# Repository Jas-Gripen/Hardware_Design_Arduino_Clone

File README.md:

# Hardware_Design_Arduino_Clone
I made schematics for an Arduino Clone in KiCad.
There is a description of why I chosed to design the board like I did in the PCB_Report.pdf file.

The original schematic (only Eeschema type) are avalible here: https://www.arduino.cc/en/uploads/Main/arduino_NG_schematic.png
The placement of the components as well as the version of them are of my own choosing. The same goas for the PCB-traces and vias.

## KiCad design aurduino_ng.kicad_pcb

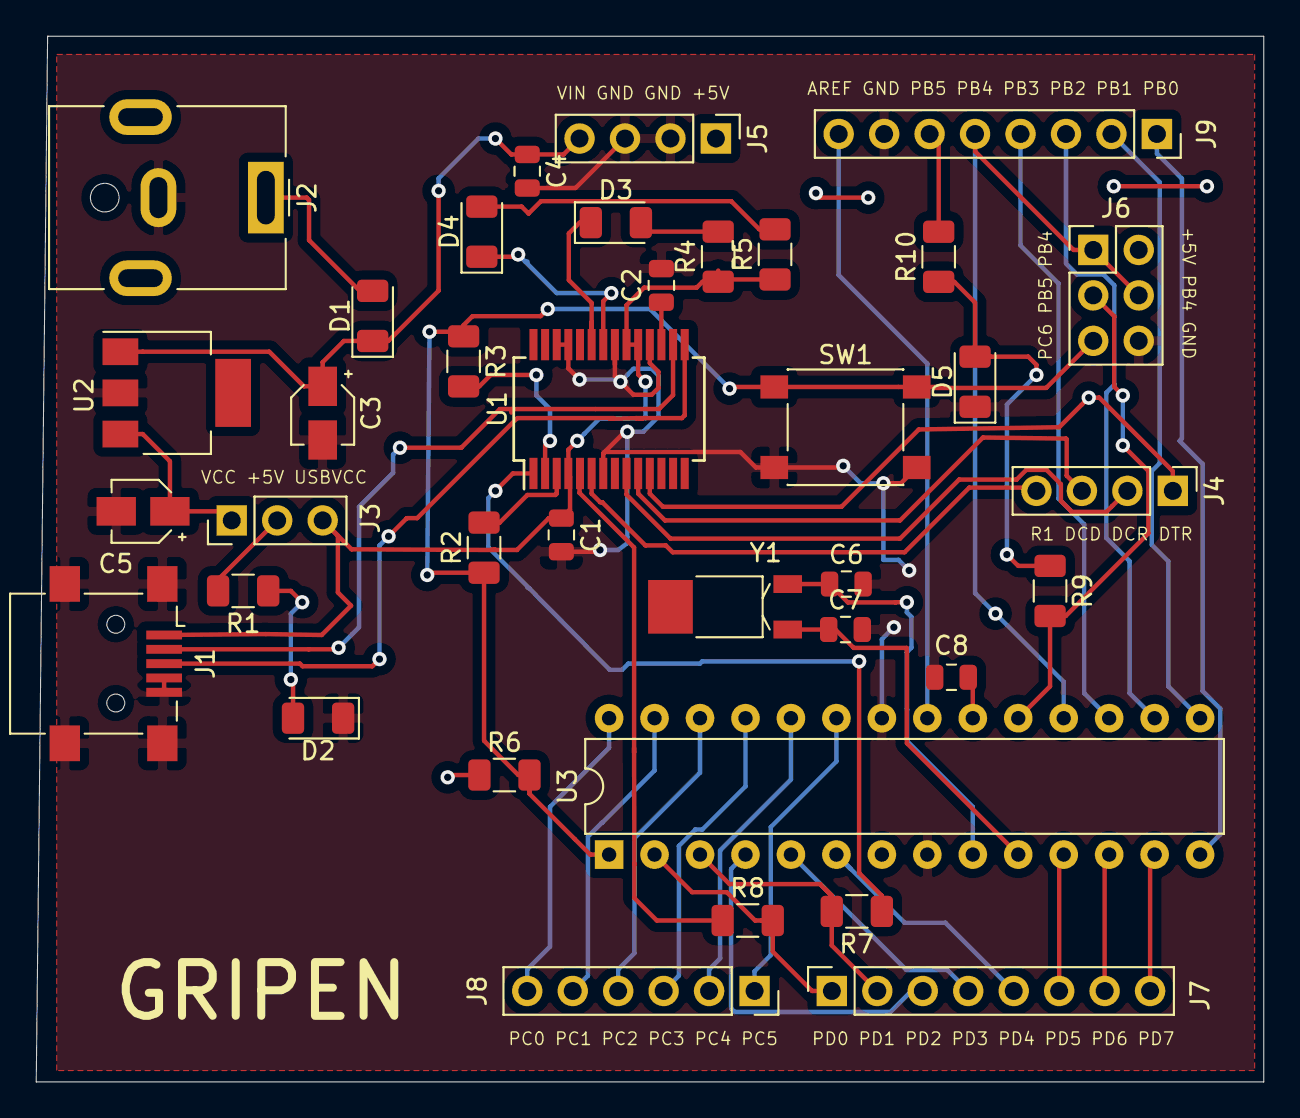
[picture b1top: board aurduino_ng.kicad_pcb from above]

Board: 2 copper layers, 68.6 x 58.4 mm, 37 parts (0 on the bottom side), 48 nets.

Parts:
C1, C2, C4, C8: 100n; C_0805_2012Metric
C3, C5: 100u; CP_Elec_3x5.3
C6, C7: 22p; C_0805_2012Metric
D1, D2, D3, D4, D5: LED; LED_1206_3216Metric
J1: USB_B_Mini; USB_Mini-B_Lumberg_2486_01_Horizontal
J2: Barrel_Jack_Switch; BarrelJack_CUI_PJ-063AH_Horizontal
J3: Conn_01x03; PinHeader_1x03_P2.54mm_Vertical
J4, J5: Conn_01x04; PinHeader_1x04_P2.54mm_Vertical
J6: Conn_02x03_Odd_Even; PinHeader_2x03_P2.54mm_Vertical
J7: Conn_01x06_Female; PinSocket_1x06_P2.54mm_Vertical
J8, J9: Conn_01x08_Female; PinSocket_1x08_P2.54mm_Vertical
R1, R9, R10: 470; R_1206_3216Metric
R2, R3: 100; R_1206_3216Metric
R4, R5: 220; R_1206_3216Metric
R6: 10k; R_1206_3216Metric
R7, R8: 1k; R_1206_3216Metric
SW1: SW_DIP_x01; SW_SPST_PTS645
U1: FT232RL_my; SSOP-28_5.3x10.2mm_P0.65mm
U2: L7805; SOT-223
U3: ATmega8-16PU; DIP-28_W7.62mm
Y1: 16MHz; Crystal_SMD_MicroCrystal_MS1V-T1K

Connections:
+5V: C8.1, J3.2, J5.1, J6.2, R1.2, R6.1, U3.7, U3.20
/AREF: J9.8, U3.21
/M8RXD: R8.1, U1.5
/M8TXD: R7.1, U1.1
/PB4: J6.1, J6.4, J9.5, U3.18
/PB5: J6.3, R9.2, U3.19
/PD0: J8.1, R8.2, U3.2
/PD1: J8.2, R7.2, U3.3
/USBVCC: C1.1, J1.1, J3.3, R4.1, R5.1, U1.4, U1.19, U1.20
/VCC: C5.1, J3.1, U2.3
/VIN: C3.1, C4.1, D1.1, J5.4, U2.1
GND: C1.2, C2.2, C3.2, C4.2, C5.2, C6.2, C7.2, C8.2, D2.1, D5.1, J1.4, J1.5, J1.6, J2.2, J5.2, J5.3, J6.6, J9.7, SW1.2, U1.7, U1.18, U1.21, U1.25, U1.26, U2.2, U3.8, U3.22
unnamed: C2.1, U1.17
unnamed: C6.1, U3.9, Y1.1
unnamed: C7.1, U3.10, Y1.2
unnamed: D1.2, J2.1
unnamed: D2.2, R1.1
unnamed: D3.1, U1.23
unnamed: D3.2, R4.2
unnamed: D4.1, U1.22
unnamed: D4.2, R5.2
unnamed: D5.2, R9.1, R10.1
unnamed: J1.2, U1.16
unnamed: J1.3, U1.15
unnamed: J4.1, U1.11
unnamed: J4.2, U1.9
unnamed: J4.3, U1.10
unnamed: J4.4, U1.6
unnamed: J6.5, R2.1, R3.1, R6.2, SW1.1, U3.1
unnamed: J7.1, U3.23
unnamed: J7.2, U3.24
unnamed: J7.3, U3.25
unnamed: J7.4, U3.26
unnamed: J7.5, U3.27
unnamed: J7.6, U3.28
unnamed: J8.3, U3.4
unnamed: J8.4, U3.5
unnamed: J8.5, U3.6
unnamed: J8.6, U3.11
unnamed: J8.7, U3.12
unnamed: J8.8, U3.13
unnamed: J9.1, U3.14
unnamed: J9.2, U3.15
unnamed: J9.3, U3.16
unnamed: J9.4, U3.17
unnamed: J9.6, R10.2
unnamed: R2.2, U1.3
unnamed: R3.2, U1.2

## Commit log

2021-04-23 Pushed all the files
2021-04-23 Pushed png files, schematics and 3D board
2021-04-23 Moved files into folders
2021-04-23 Added the PCB Report
